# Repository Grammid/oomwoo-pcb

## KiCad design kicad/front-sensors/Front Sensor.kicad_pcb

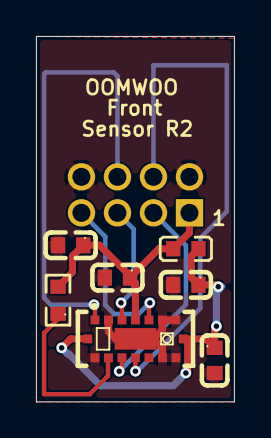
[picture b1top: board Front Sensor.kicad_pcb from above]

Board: 2 copper layers, 11.0 x 20.3 mm, 8 parts (1 on the bottom side), 9 nets.

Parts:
C2001, C2003: 10uF/10V; C0603
C2002, C2004: 100nF/50V; C0603
J2001: 2005WR-2x4P; HDR-TH_8P-P2.00-H-F-R2-C2-S2.00-W8.8
L2001: BLM18PG121SN1D
R2001: 47k; R0603
U2001: VL53L7CHV0GC/1; VL53L7CHV0GC_1

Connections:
/I2C_RST: J2001.6, U2001.A1 (I2C_RST)
/INT: J2001.5, U2001.A3 (INT)
/SCL: J2001.4, U2001.C4 (SCL)
/SDA: J2001.3, U2001.C3 (SDA)
/~LPn: J2001.7, U2001.A5 (LPn)
GND: C2001.2, C2002.2, C2003.2, C2004.2, J2001.2, J2001.8, U2001.A2 (RSVD4), U2001.A6 (RSVD1), U2001.A7 (RSVD2), U2001.B4 (THERMALPAD), U2001.C1 (GND), U2001.C6 (RSVD3), U2001.C7 (GND)
unnamed: R2001.1, U2001.C2 (RSVD6)
VAA-3V3: C2001.1, C2002.1, L2001.2, U2001.B1 (AVDD), U2001.B7 (AVDD)
VDD-3V3: C2003.1, C2004.1, J2001.1, L2001.1, R2001.2, U2001.A4 (IOVDD)
